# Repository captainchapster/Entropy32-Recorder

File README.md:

# Entropy32 Recorder

Firmware, hardware, and tooling for the Entropy32 Recorder — a standalone
Geiger-counter-based board, built around an ATmega328P (Arduino Nano form
factor), for recording raw entropy source data.

This is a **separate board from Entropy32 / Entropy32 Plus**, not a mode or
alternate firmware of it. It does not generate seeds or any conditioned
output. Its only job is to capture raw, unconditioned edge timing data from
the entropy source (Geiger tube + LM393 comparator) so it can be run through
statistical test suites (e.g. NIST STS) to validate the quality of the
entropy source itself, before that source is trusted for use in Entropy32
Plus's seed generation.

## Repository layout

- **`entropy32_evidence_protocol.md`** — the SP 800-90B reproducible
  evidence protocol these tools implement: capture requirements, the
  raw/derived evidence package layout, exact firmware reconstruction
  semantics, and the pinned NIST toolchain invocation.
- **`entropy32_recorder.ino`** — the recorder's firmware. It timestamps
  every rising edge on D2 (post-LM393 comparator output) and streams
  `edge_index,timestamp_us` CSV rows over serial. It does no filtering,
  interval pairing, or SHA-256 conditioning by design — it's for capturing
  raw edge timing data only, unmodified, for statistical testing.
- **`tools/capture_serial_to_csv.py`** — reads the serial stream produced by
  the sketch above and writes it to a CSV file matching the evidence
  protocol's `raw/raw_edges.csv` shape (`edge_index`, `raw_timer_ticks`,
  `monotonic_timestamp_us`). `raw_timer_ticks` is the board's `micros()`
  reading exactly as received (wraps every ~71.58 min);
  `monotonic_timestamp_us` is that value unwrapped into an ever-increasing
  64-bit microsecond count, reconstructed on the host (via
  `tools/edge_timing.py`) so the firmware/ISR stays minimal. Every row is
  flushed and fsynced to disk as soon as it's written — negligible cost at
  this source's event rate, and each edge is an irreplaceable physical
  event, so nothing is ever buffered short of an actual power loss. One
  capture is one continuous, uninterrupted run from edge 0 — per the
  evidence protocol, there is no resume; the tool refuses to run at all
  if `--out` already has data, and an interrupted capture must be
  restarted under a new `--out` rather than continued. On a fully
  complete run, also writes a `capture_status.json` sibling (e.g.
  `raw_edges.status.json`) recording edge count, start/end UTC
  timestamps, and the zero overrun/drop counts implied by reaching that
  point at all — this feeds `tools/package_evidence.py` and the
  protocol's `capture_status.json` (§4). Requires `pyserial`.
- **`tools/edge_timing.py`** — the timer-wrap-unwrapping math used by the
  capture tool, in its own module mainly so it can be tested in isolation.
- **`tools/check_edges.py`** — pre-flight sanity check for a captured CSV:
  confirms `edge_index`/`monotonic_timestamp_us` are well-formed, and
  compares the inter-arrival distribution against a Poisson expectation to
  flag comparator bounce/chatter. Run this before feeding a capture into
  NIST STS / SP 800-90B tooling:
  `python tools/check_edges.py tools/raw_edges.csv`.
- **`tools/derive_evidence.py`** — reconstructs Entropy32's actual
  bit-extraction (200us reject filter, non-overlapping interval pairing,
  second-longer=1/second-shorter=0, ties discarded) per
  `entropy32_evidence_protocol.md` §5,
  producing the protocol's `derived/` package — `all_intervals_us.csv`,
  `firmware_accepted_intervals_us.csv`, `comparison_bits.bin`,
  `derivation_report.json`.
  `python tools/derive_evidence.py tools/raw_edges.csv --out-dir tools/derived --source-dir ../entropy32_plus`.
  `comparison_bits.bin` is ready for `ea_non_iid -i -v comparison_bits.bin 1`
  (bits_per_symbol=1, per the protocol's §8 — not a byte-per-symbol
  truncation). `--source-dir` (optional but recommended) points at a local
  checkout of the firmware these constants are claimed to match, and
  auto-fills `derivation_report.json`'s `source_repo`/`source_commit`/
  `entropy32_firmware_blob_sha` from its git metadata and `.ino` hash —
  left `"unknown"` rather than guessed if omitted.
- **`tools/package_evidence.py`** — assembles the protocol's immutable
  evidence directory (§4) from a capture, a `derive_evidence.py` run, and
  a separately-run `ea_non_iid` pass: copies `raw/` and `derived/` in,
  records the exact NIST command/toolchain/exit status under `nist/`,
  writes `capture_status.json` and a `manifest.json` (fields it can't
  know from the data — hardware, physical source, environment — are
  filled from `setup.json` via `--setup`, otherwise left `null`), and
  computes a `SHA256SUMS` covering every file in the package.
- **`tools/verify_evidence.py`** — independently checks a finished
  package: hashes, raw structure, a byte-for-byte re-derivation, and the
  saved NIST run. The one command a replicator needs.
- **`tools/make_evidence.py`** — runs everything from a finished capture
  to a verified package (check, derive, NIST via WSL, package, verify).
- **`setup.json`** — the recording rig's description (manifest fields)
  and local tool paths, read by `make_evidence.py`.
- **`KiCad/`** — PCB design (schematic, layout, 3D models, and
  fabrication/production outputs for the Entropy32 Recorder board).

## Hardware

The board pairs a Geiger tube's LM393 comparator output with an ATmega328P
(D2, using the board's existing pull-down for bias). Design files are in
[`KiCad/`](KiCad/), including BOM, designators, netlist, and pick-and-place
files under `KiCad/production/`.

## Usage

All commands below run from the repo root (`entropy32_recorder/`).

### Verifying a published package

If you're checking someone else's result, this is the only command you
need (Python 3.8+, no dependencies):

```
python tools/verify_evidence.py entropy32_sp80090b_2026-10-03a
```

It checks every file against `SHA256SUMS`, checks the raw capture's
structure (no missing edges, consistent timer unwrapping), re-derives the
bit stream from `raw/raw_edges.csv` and requires it to match byte for
byte, and checks the saved NIST output belongs to this package's
`comparison_bits.bin` and reports all ten estimators. It ends with
`VERIFIED`, `VERIFIED as a PILOT package` (consistent, but below the
protocol's 1,000,000-sample gate), or `FAILED`, and exits non-zero on
failure. Two optional, slower checks:

```
python tools/verify_evidence.py entropy32_sp80090b_2026-10-03a \
  --firmware-dir ../entropy32_plus \
  --ea-non-iid ~/SP800-90B_EntropyAssessment/cpp/ea_non_iid
```

`--firmware-dir` (any clone of
[Entropy32-Plus](https://github.com/captainchapster/Entropy32-Plus))
confirms the firmware at the commit the derivation claims is the one whose
hash is recorded. `--ea-non-iid` re-runs NIST (built as below) and
requires identical output; on Windows a `~/...` or `/...` path runs inside
WSL automatically.

### One-time setup for recording

1. Flash `entropy32_recorder.ino` to the board, and `pip install pyserial`.
2. Clone the Entropy32 firmware next to this repo, so the derivation can
   be pinned to it: `git clone https://github.com/captainchapster/Entropy32-Plus.git ../entropy32_plus`
3. Build the pinned NIST tool. `ea_non_iid` is a Linux build — on Windows
   use [WSL](https://learn.microsoft.com/en-us/windows/wsl/install)
   (`wsl --install`, one-time) and run this inside it:

   ```bash
   sudo apt update && sudo apt install -y build-essential libbz2-dev
   git clone https://github.com/usnistgov/SP800-90B_EntropyAssessment.git
   cd SP800-90B_EntropyAssessment
   git checkout 68ed165fd7a3eeef26b87a546ba23f338e82a3f3  # pinned v1.1.8, see protocol §8
   make
   cd selftest && ./selftest && cd ..
   make non_iid
   ```

4. Edit [`setup.json`](setup.json): `tools` points at the firmware
   checkout and the built `cpp/ea_non_iid`; `manifest` describes your rig
   (detector, source, environment — `null` for anything unknown, never a
   guess); `check_edges.dead_time_ns` is your detector's dead time, if
   known. These are written into every package, so you describe the
   setup once, not per capture.

### Recording a capture

1. Run the capture:

   ```
   python tools/capture_serial_to_csv.py --port COM5 --out tools/raw_edges.csv
   ```

   (`COM5` on Windows, `/dev/ttyUSB0` on Linux.) By default it runs until
   the protocol's stop gate — 1,000,000 comparison bits, counted live
   with the same reconstruction the derivation uses — so it can't stop one
   bit short the way a fixed edge count can (2,000,000 edges yields only
   999,999 bits). For a quick smoke test use `--count 2000` instead.

   If the board reports `OVERRUN_DETECTED` or the capture stops for any
   other reason, that run is invalid — one capture is one continuous run
   from edge 0, with no resume. Start over.
2. Build and verify the evidence package:

   ```
   python tools/make_evidence.py
   ```

   This runs the edge sanity check, the derivation, NIST (through WSL on
   Windows), packaging and verification, recording the NIST tool's commit
   and compiler from the build itself. It refuses to package an
   incomplete capture or an unpinned/modified NIST build. The package is
   named from the capture's start date, e.g. `entropy32_sp80090b_2026-11-20a/`.
3. Commit the package directory it prints. Once committed it's immutable
   — never edit it; a new capture gets a new package.

### Running the steps by hand

`make_evidence.py` only strings together tools you can also run
yourself, e.g. to inspect an intermediate result:

```
python tools/check_edges.py tools/raw_edges.csv --dead-time-ns 720000
python tools/derive_evidence.py tools/raw_edges.csv --out-dir tools/derived --source-dir ../entropy32_plus
# in WSL, from SP800-90B_EntropyAssessment/cpp, save stdout/stderr/exit status verbatim:
./ea_non_iid -i -v /mnt/d/Programming/entropy32_recorder/tools/derived/comparison_bits.bin 1
python tools/package_evidence.py --raw tools/raw_edges.csv --derived-dir tools/derived \
  --capture-id <id> --setup setup.json --nist-command "<exact command>" \
  --nist-stdout <file> --nist-stderr <file> --nist-exit-status <n> \
  --nist-compiler-version "<compiler>"
python tools/verify_evidence.py entropy32_sp80090b_<id>
```

## Known limitations / best practices for a full campaign

- **Sample size**: a few thousand edges (a few hours at typical background
  rates) is only enough for a pipeline smoke test. SP 800-90B-style
  min-entropy estimation wants **>= 1,000,000 samples** before the result
  is meaningful — plan campaign length accordingly (at the ~16 CPM
  background rate seen in the pilot run, 1M edges is roughly 6 weeks of
  continuous capture).
- **Timestamp resolution**: `micros()` on the ATmega328P (16MHz, Timer0
  prescaler 64) only increments in steps of 4us. That's negligible at the
  observed ~3.7s mean inter-arrival time (1 part in ~10^6), so it isn't a
  concern at current event rates. If a future hardware revision moves the
  comparator output to the Timer1 input-capture pin (`ICP1` / D8 on a
  Nano) instead of D2, the ISR could latch `TCNT1` directly for
  microsecond-or-better hardware-timestamped edges with no software ISR
  jitter — worth considering for a higher-throughput source, but out of
  scope for the current board (D2 is fixed on the fabricated PCB).
- **Comparator bounce**: `check_edges.py` compares the inter-arrival
  distribution against the Poisson process a radioactive source should
  produce; a pileup of anomalously short gaps indicates LM393 output
  chatter rather than genuine independent events. No bounce was observed
  in the pilot 2000-edge run.

## License

- Firmware and software (`entropy32_recorder.ino`, `tools/`): [MIT](LICENSE)
- Hardware (`KiCad/`): [CERN-OHL-S v2](LICENSE-HARDWARE)

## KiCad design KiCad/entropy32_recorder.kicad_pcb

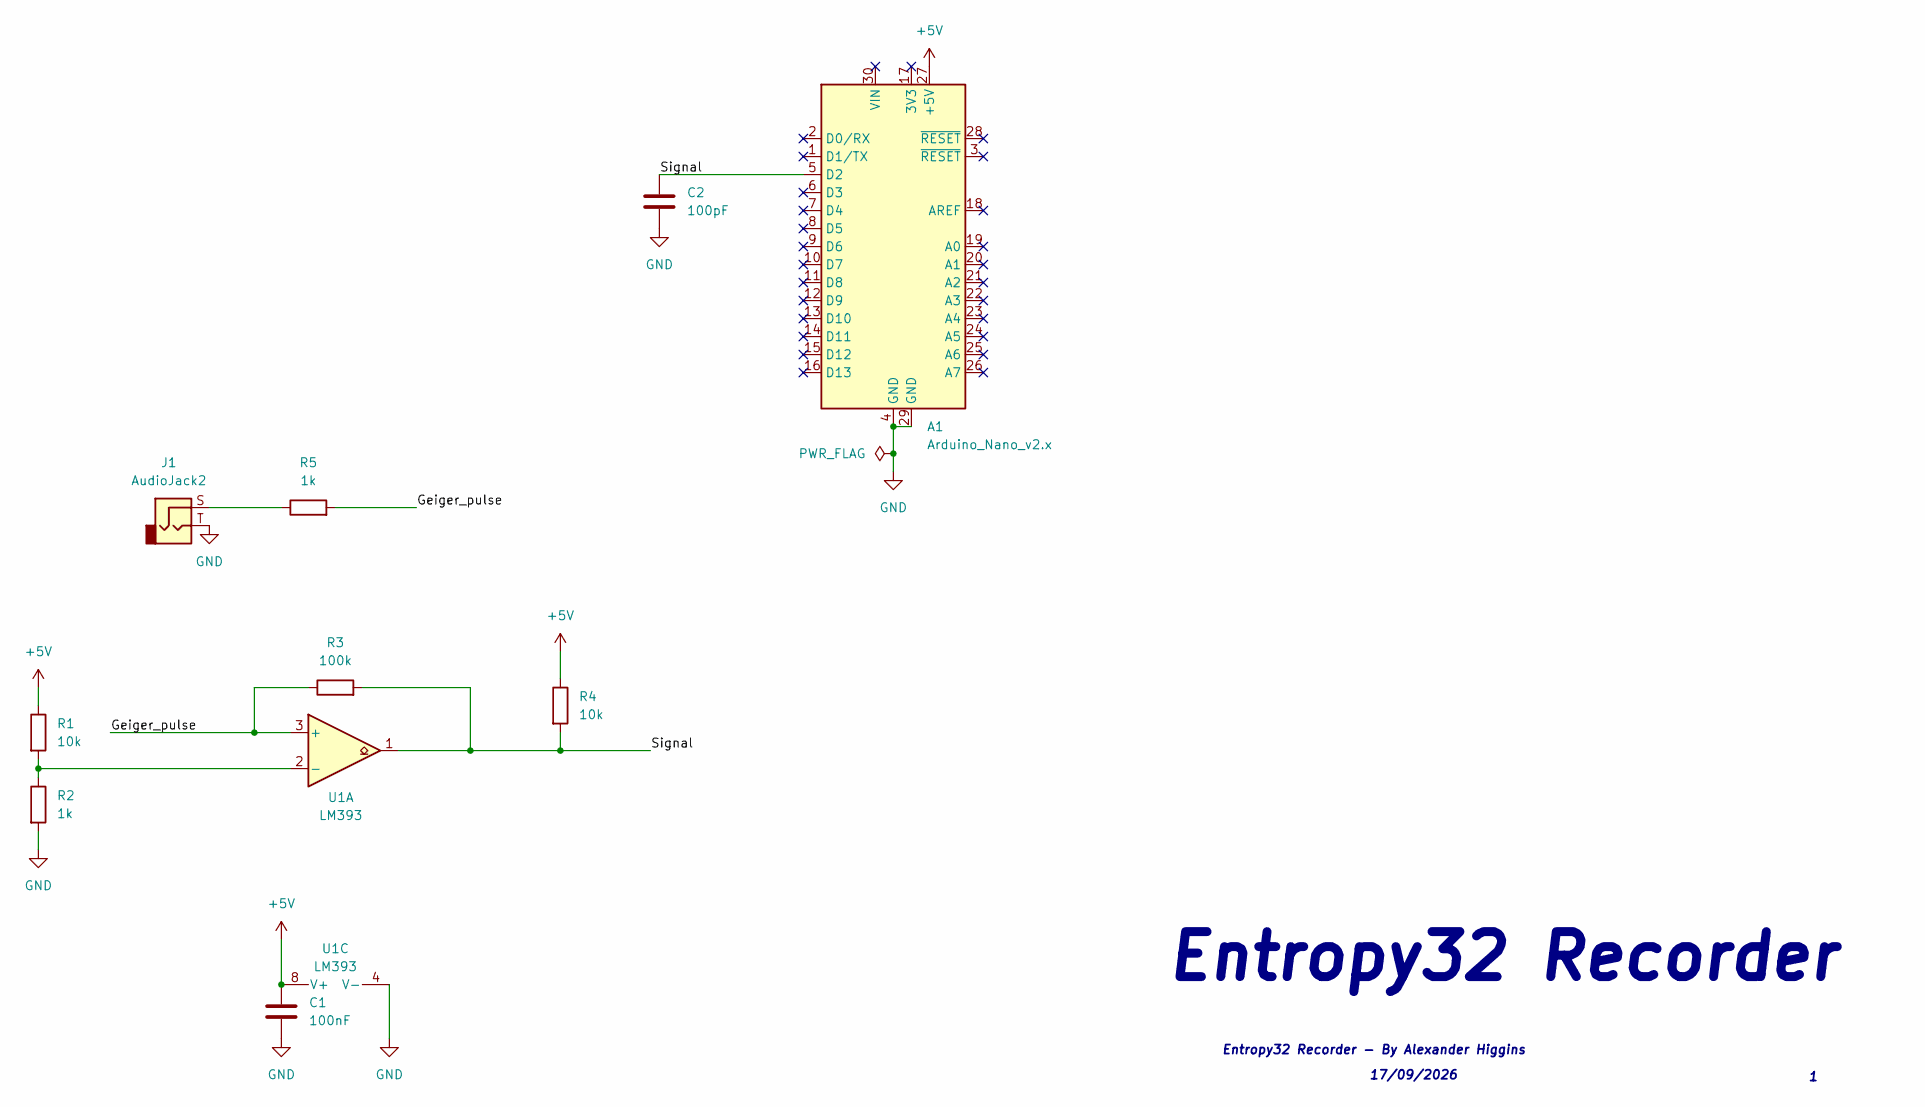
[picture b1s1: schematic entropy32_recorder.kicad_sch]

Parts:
A1: Arduino_Nano_v2.x; Arduino_Nano
C1: 100nF; C_Disc_D5.0mm_W2.5mm_P5.00mm
C2: 100pF; C_Disc_D5.0mm_W2.5mm_P5.00mm
J1: AudioJack2; Jack_3.5mm_PJ320E_Horizontal
R1, R4: 10k; R_Axial_DIN0207_L6.3mm_D2.5mm_P7.62mm_Horizontal
R2, R5: 1k; R_Axial_DIN0207_L6.3mm_D2.5mm_P7.62mm_Horizontal
R3: 100k; R_Axial_DIN0207_L6.3mm_D2.5mm_P7.62mm_Horizontal
U1: LM393; DIP-8_W7.62mm

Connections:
+5V: A1.27 (+5V), C1.1, R1.1, R4.1, U1.8 (V+)
/Geiger_pulse: R3.1, R5.2, U1.3 (+)
/Signal: A1.5 (D2), C2.2, R3.2, R4.2, U1.1
GND: A1.4 (GND), A1.29 (GND), C1.2, C2.1, J1.T, R2.2, U1.4 (V-)
unnamed: J1.S, R5.1
unnamed: R1.2, R2.1, U1.2 (-)

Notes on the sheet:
Entropy32 Recorder - By Alexander Higgins
Entropy32 Recorder
17/09/2026

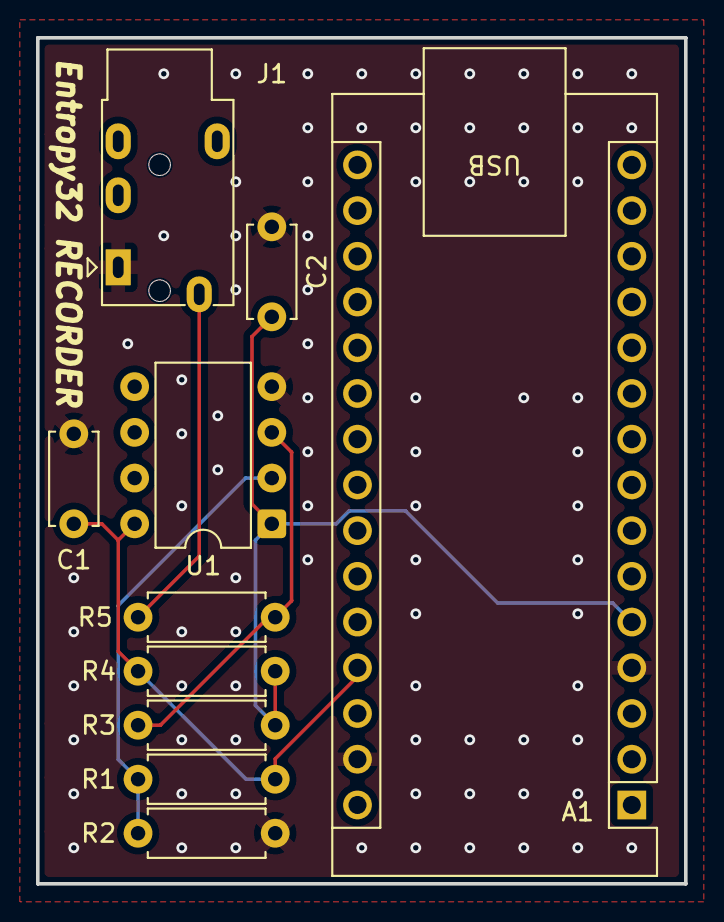
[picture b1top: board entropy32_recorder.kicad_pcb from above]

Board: 2 copper layers, 36.0 x 47.0 mm, 10 parts (0 on the bottom side), 6 nets.
